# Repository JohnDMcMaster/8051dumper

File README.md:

# 8051dumper: Dump ROM contents from unprotected 8051 series processors.

This board and firmware allow the mask-programmed ROM contents to be dumped from
[Intel 8051 processors](https://en.wikipedia.org/wiki/Intel_MCS-51) and
derivatives/clones which do not include ROM readout protection mechanisms.

## Description

I wanted to dump out the firmware from the internal mask ROM of a Signetics
SCN8051H microcontroller in an ailing Micropolis 1325 (AKA DEC RD53-A) hard disk
drive. None of my programmers are able to do that, but there's a tricky way to
get early 8051 microcontrollers to dump out their own firmware. I made this
board to do it... and over-engineered the heck out of it, because why not! This
technique has been around for a long time. I didn't invent it. I just made this
board because I'd rather lay out a board than wire up stuff on a breadboard.

The 8051 has a pin called EA\# which tells it whether to fetch code from its
internal ROM (which is programmed at the metal mask layer at chip fabrication
time) or an external ROM. The trick is to put the 8051 into a circuit which
initially pulls EA\# low, so that the 8051 will boot from an external ROM with
our dumper code in it. That code immediately jumps out of the 4k address range
that is mapped to internal ROM when EA\# is high, and then uses a GPIO pin to
pull its own EA\# pin high and re-enable the internal mask ROM. At that point,
the 8051 conveniently fetches program memory accesses in the 0x0000-0x0FFF range
from the internal ROM, and fetches program memory accesses outside that range
from our external ROM. The special dumper code on our external ROM can then use
the MOVC function to read internal ROM bytes, and then dump them out somehow
(such as with the built-in serial port).

The 8052, 8054 and 8058 chips have larger internal ROM spaces, but otherwise
work the same way. Just for the heck of it, I put a knob on this board to tell
its firmware how much of the internal ROM space it should try to dump.

Later 8051 derivatives added features to prevent dumping their internal ROMs
easily, sunce as simply latching EA\# at reset time so that changing it later
doesn't do anything. This board can't work with any of those. It's only intended
to work with original Intel 8051 microcontrollers and exactl clones whose EA\#
pins behave the same way.

## Building the Board

You're on your own for assembling the board. You will need to program the
board's firmware into an AT28C256 (or plug-in equivalent) 32k x 8 (E(E))PROM.
Use the `firmware/8051dumper_filled.hex` image. This image contains the
necessary firmware for the 8051dumper board, with its unused areas filled with a
recognizable pattern to help you identify whether any given device under test is
dumping internal or external ROM contents.

## Using the Board

This board requires an external source of clean, regulated 5 VDC power, and some
sort of asynchronous serial interface with 5V TTL/CMOS signal levels. An FTDI
TTL-232R-5V cable can be pluged right into the header, or you can use clip
leads. The silkscreen markings identify the ground pin and the two data pins.

**There is no reverse-polarity protection, power regulation, or overvoltage protection on this board.** You need to connect the power correctly, or you will fry stuff. You can supply power through either the barrel jack or with clip leads
connected to the two test points.

Set your serial interface for 9600 baud, 8 data bits, no parity, and no flow
control. Use a terminal emulator or any other suitable software which can
capture the 9600 baud stream from 8051dumper.

Always make sure that the power switch is **OFF** before installing or removing
a device under test from 8051dumper.

If all goes well, when you turn on the board with a working [8051 (or other
MCS-51 series)](https://en.wikipedia.org/wiki/Intel_MCS-51) microcontroller
installed, the green START button will begin blinking and the serial port will
spit out `8051dumper v1.0 by NF6X`. If that doesn't happen at power-on, try
pressing the red RESET button to reset the microcontroller manually. If it still
doesn't happen, start debugging. Maybe the socket isn't making good contact?
Maybe, well, literally anything else has gone wrong?

Once the green START button is blinking, set the knob to the appropriate ROM
size and then press the green START button to begin the dump. While the dump is
in progress, the red RESET button will flash rapidly. When the dump is done, the
red RESET button will go dark and the green START button will light up. Now you
can turn off the board, or press RESET to do it all over again.

The 8051dumper output is in [Intel hex](https://en.wikipedia.org/wiki/Intel_HEX)
format. If you try dumping beyond the end of the internal ROM, or if you try
dumping from a device which latches EA\# at reset time, then some or all of the
output will be from the 8051dumper's own external ROM instead of the device
under test's internal ROM. To help you indentify when this happens, the unused
spaces of 8051dumper's ROM are filled with a pattern which is recognizable in
either hexadecimal or ASCII representations, and repeats every 16 bytes:

* Address (2 bytes)
* 0x00
* 0x80
* 0x51
* 0x00
* "8051dumper"

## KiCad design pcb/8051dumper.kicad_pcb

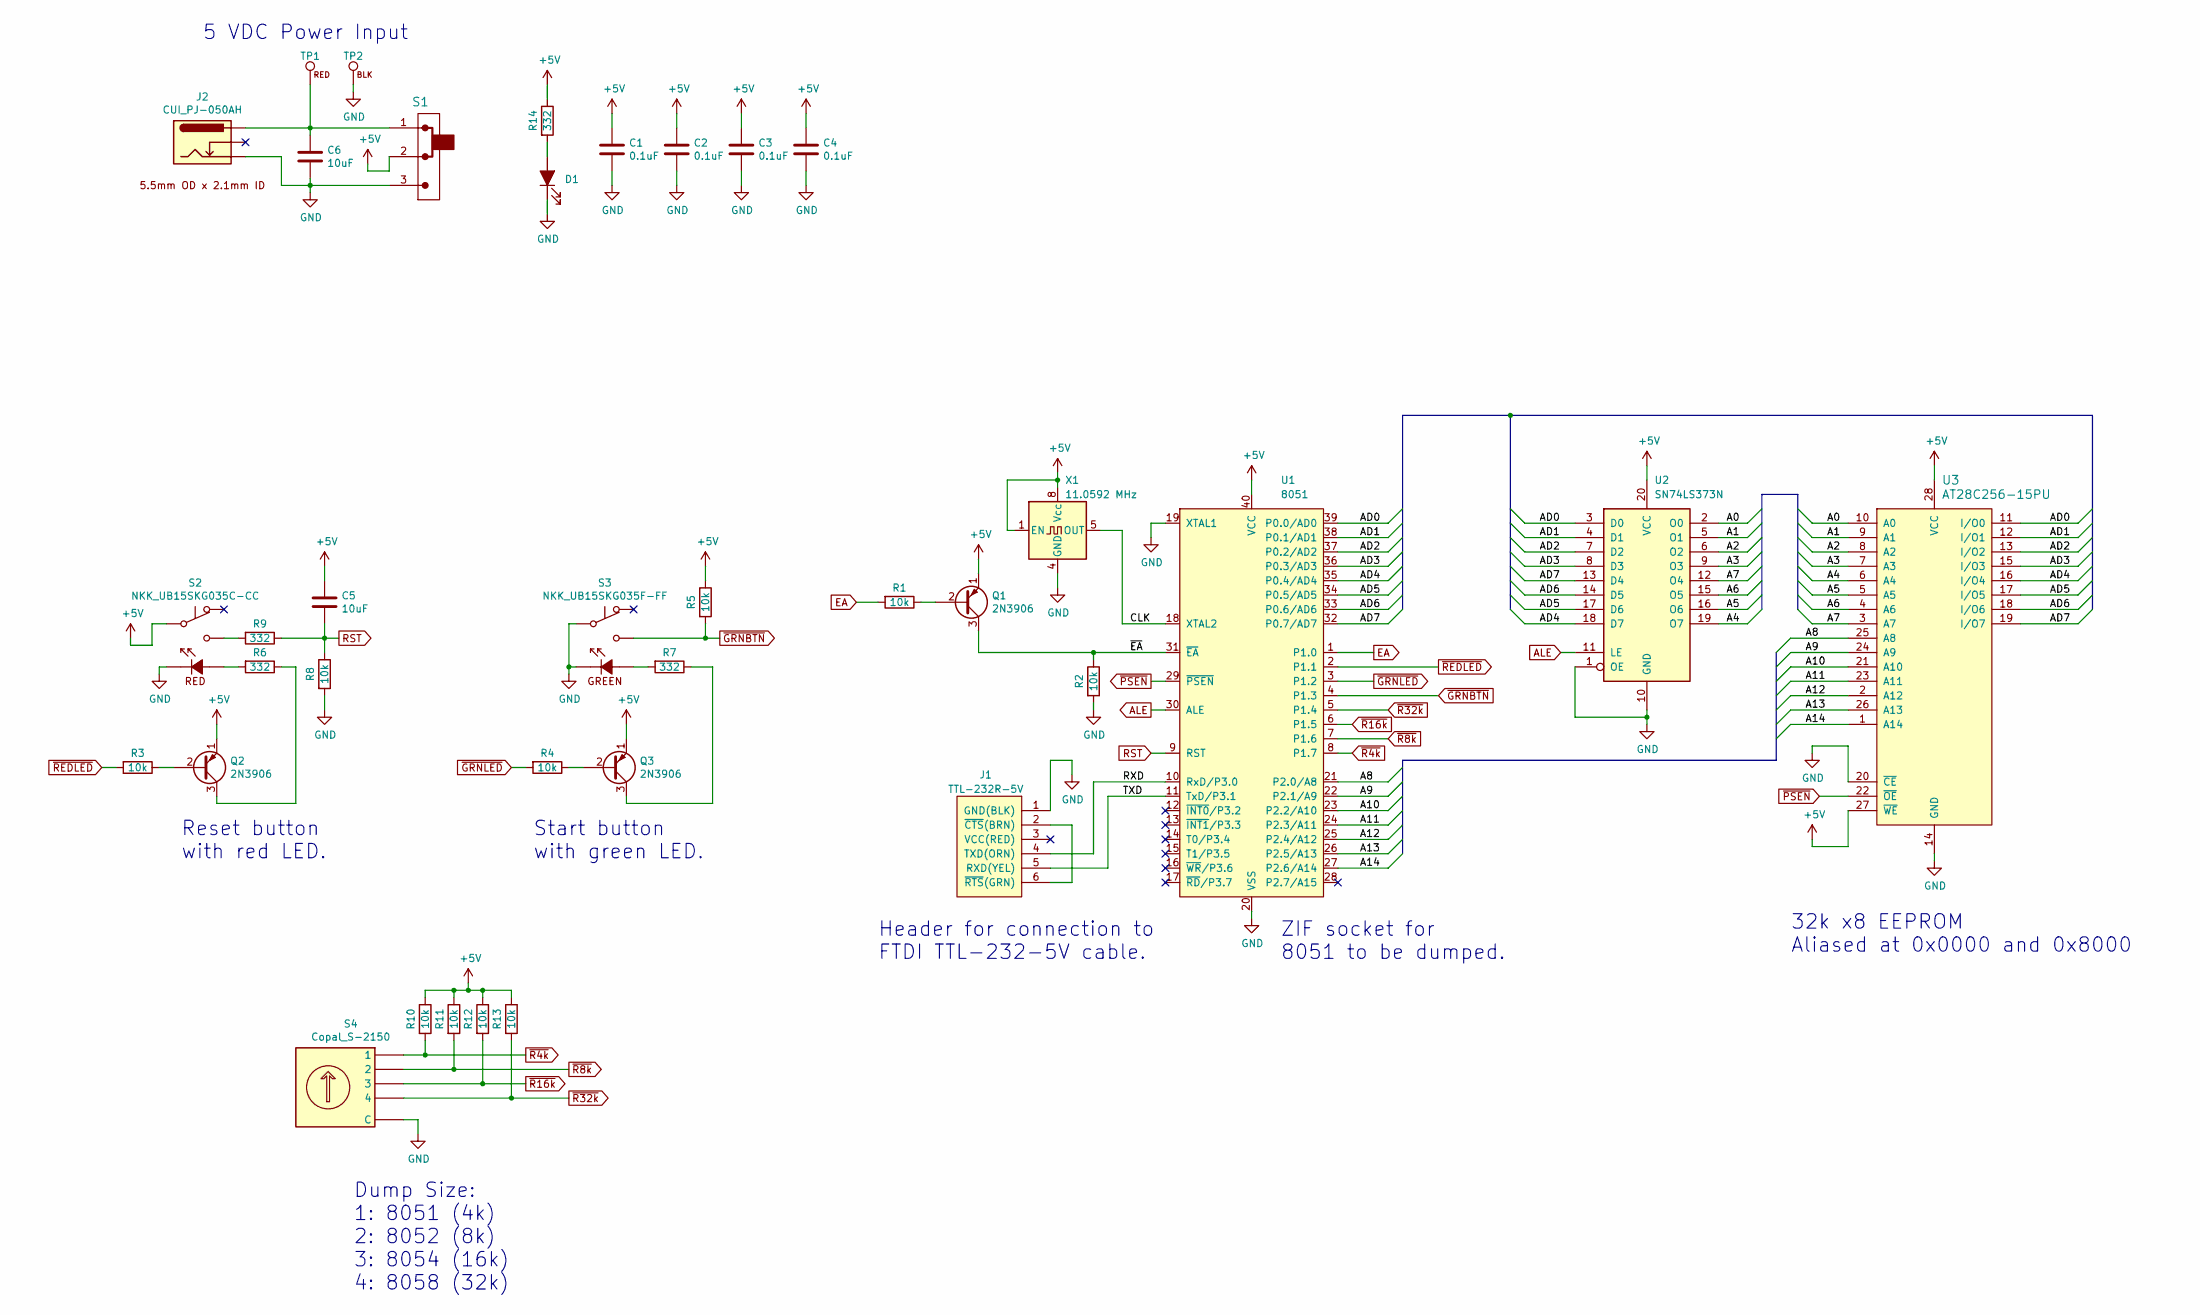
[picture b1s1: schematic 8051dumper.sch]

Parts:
C1, C2, C3, C4: 0.1uF; C_Disc_D3.8mm_W2.6mm_P2.50mm; MPN Vishay:K104K10X7RF5UL2
C5, C6: 10uF; C_Disc_D5.1mm_W3.2mm_P5.00mm; MPN TDK:FG24X7R1A106KRT06
D1: WP7113GD; LED_D5.0mm_Green_Kingbright_WP7113; MPN Kingbright:WP7113GD
J1: TTL-232R-5V; PinHeader_1x6_P2.54mm_Vertical_Unshrouded; MPN Sullins:PBC06SAAN
J2: CUI_PJ-050AH; BarrelJack_Horizontal_CUI_PJ-050AH; MPN CUI:PJ-050AH
Q1, Q2, Q3: 2N3906; TO-92_Inline_Wide; MPN ON Semiconductor:2N3906TF
R1, R2, R3, R4, R5, R8, R10, R11, R12, R13: 10k; R_Axial_DIN0207_L6.3mm_D2.5mm_P10.16mm_Horizontal; MPN Stackpole:RNF14FTD10K0
R6, R7, R9, R14: 332; R_Axial_DIN0207_L6.3mm_D2.5mm_P10.16mm_Horizontal; MPN Stackpole:RNF14FTD332R
S1: CK_1101M2S3CQE2; SW_CK_1101M2S3CQE2; MPN CK:1101M2S3CQE2
S2: NKK_UB15SKG035C-CC; SW_NKK_UB15SKG035C-CC; MPN NKK:UB15SKG035C-CC
S3: NKK_UB15SKG035F-FF; SW_NKK_UB15SKG035F-FF; MPN NKK:UB15SKG035F-FF
S4: Copal_S-2150; MPN Copal:S-2150
TP1: TestPoint_Mini_Red; TestPoint_Keystone_5000; MPN Keystone:5000
TP2: TestPoint_Mini_Black; TestPoint_Keystone_5001; MPN Keystone:5001
U1: 8051; DIP-40_W15.24mm_ZIF_Socket_Aries_40-6554-10; MPN Aries:40-6554-10
U2: SN74LS373N; DIP-20_W7.62mm; MPN TI:SN74LS373N
U3: AT28C256-15PU; DIP-28_W15.24mm_Socket; MPN Microchip:AT28C256-15PU
X1: 11.0592 MHz; Oscillator_DIP-8; MPN ECS:ECS-2200BX-110.5

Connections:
+5V: C1.1, C2.1, C3.1, C4.1, C5.1, Q1.1 (E), Q2.1 (E), Q3.1 (E), R5.1, R10.1, R11.1, R12.1, R13.1, R14.1, S1.2, S2.1 (COM), U1.40 (VCC), U2.20 (VCC), U3.27 (~WE), U3.28 (VCC), X1.1 (EN), X1.8 (Vcc)
/A0: U2.2 (O0), U3.10 (A0)
/A1: U2.5 (O1), U3.9 (A1)
/A2: U2.6 (O2), U3.8 (A2)
/A3: U2.9 (O3), U3.7 (A3)
/A4: U2.19 (O7), U3.6 (A4)
/A5: U2.16 (O6), U3.5 (A5)
/A6: U2.15 (O5), U3.4 (A6)
/A7: U2.12 (O4), U3.3 (A7)
/A8: U1.21 (P2.0/A8), U3.25 (A8)
/A9: U1.22 (P2.1/A9), U3.24 (A9)
/A10: U1.23 (P2.2/A10), U3.21 (A10)
/A11: U1.24 (P2.3/A11), U3.23 (A11)
/A12: U1.25 (P2.4/A12), U3.2 (A12)
/A13: U1.26 (P2.5/A13), U3.26 (A13)
/A14: U1.27 (P2.6/A14), U3.1 (A14)
/AD0: U1.39 (P0.0/AD0), U2.3 (D0), U3.11 (I/O0)
/AD1: U1.38 (P0.1/AD1), U2.4 (D1), U3.12 (I/O1)
/AD2: U1.37 (P0.2/AD2), U2.7 (D2), U3.13 (I/O2)
/AD3: U1.36 (P0.3/AD3), U2.8 (D3), U3.15 (I/O3)
/AD4: U1.35 (P0.4/AD4), U2.18 (D7), U3.16 (I/O4)
/AD5: U1.34 (P0.5/AD5), U2.17 (D6), U3.17 (I/O5)
/AD6: U1.33 (P0.6/AD6), U2.14 (D5), U3.18 (I/O6)
/AD7: U1.32 (P0.7/AD7), U2.13 (D4), U3.19 (I/O7)
/CLK: U1.18 (XTAL2), X1.5 (OUT)
/RXD: J1.4 (TXD(ORN)), U1.10 (RxD/P3.0)
/TXD: J1.5 (RXD(YEL)), U1.11 (TxD/P3.1)
/~EA: Q1.3 (C), R2.1, U1.31 (~EA)
ALE: U1.30 (ALE), U2.11 (LE)
EA: R1.2, U1.1 (P1.0)
GND: C1.2, C2.2, C3.2, C4.2, C6.2, D1.1 (K), J1.1 (GND(BLK)), J2.2, R2.2, R8.2, S1.3, S2.L- (K), S3.1 (COM), S3.L- (K), S4.C, TP2.1, U1.19 (XTAL1), U1.20 (VSS), U2.1 (OE), U2.10 (GND), U3.14 (GND), U3.20 (~CE), X1.4 (GND)
unnamed: C6.1, J2.1, S1.1, TP1.1
unnamed: D1.2 (A), R14.2
unnamed: J1.2 (~CTS~(BRN)), J1.6 (~RTS~(GRN))
unnamed: Q1.2 (B), R1.1
unnamed: Q2.2 (B), R3.1
unnamed: Q2.3 (C), R6.1
unnamed: Q3.2 (B), R4.1
unnamed: Q3.3 (C), R7.1
unnamed: R6.2, S2.L+ (A)
unnamed: R7.2, S3.L+ (A)
unnamed: R9.2, S2.2 (NO)
RST: C5.2, R8.1, R9.1, U1.9 (RST)
~GRNBTN: R5.2, S3.2 (NO), U1.4 (P1.3)
~GRNLED: R4.2, U1.3 (P1.2)
~PSEN: U1.29 (~PSEN), U3.22 (~OE)
~R4k: R10.2, S4.1, U1.8 (P1.7)
~R8k: R11.2, S4.2, U1.7 (P1.6)
~R16k: R12.2, S4.3, U1.6 (P1.5)
~R32k: R13.2, S4.4, U1.5 (P1.4)
~REDLED: R3.2, U1.2 (P1.1)

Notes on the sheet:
Header for connection to FTDI TTL-232-5V cable.
Reset button with red LED.
Start button with green LED.
ZIF socket for 8051 to be dumped.
5 VDC Power Input
Dump Size: 1: 8051 (4k) 2: 8052 (8k) 3: 8054 (16k) 4: 8058 (32k)
32k x8 EEPROM Aliased at 0x0000 and 0x8000

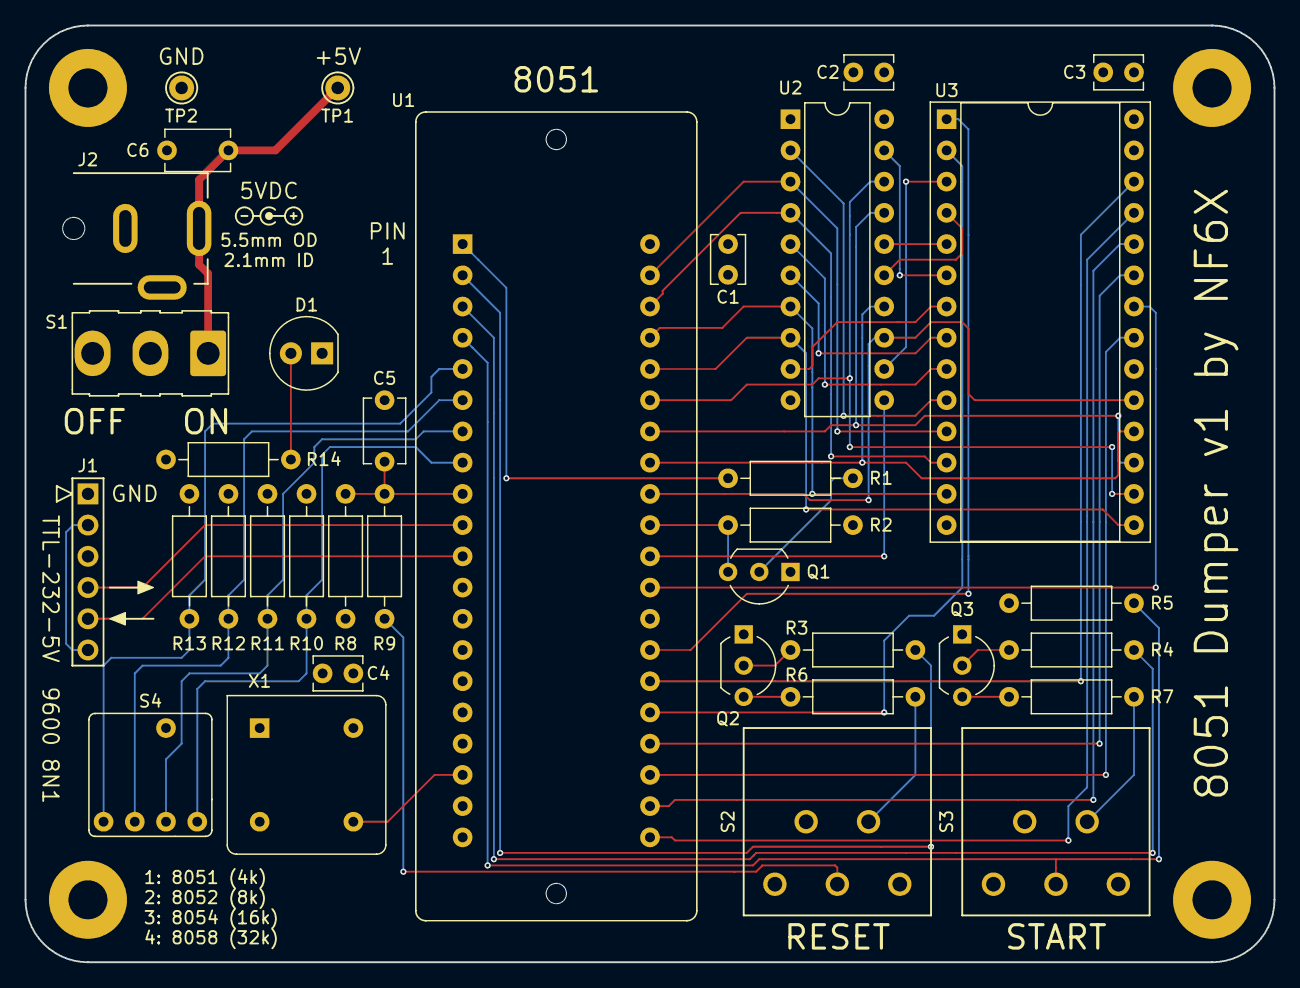
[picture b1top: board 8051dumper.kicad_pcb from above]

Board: 4 copper layers, 101.6 x 76.2 mm, 36 parts (0 on the bottom side), 51 nets.

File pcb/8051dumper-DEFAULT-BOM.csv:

MANUFACTURER,PARTNUM,QTY,REFS,IPN,VALUE,DESCRIPTION,FOOTPRINT,ALTERNATES
Aries,40-6554-10,1,U1,TBD,8051,,Package_DIP:DIP-40_W15.24mm_ZIF_Socket_Aries_40-6554-10,
CK,1101M2S3CQE2,1,S1,TBD,CK_1101M2S3CQE2,"SPDT slide switch, ON-ON",Button_Switch_THT:SW_CK_1101M2S3CQE2,
CUI,PJ-050AH,1,J2,TBD,CUI_PJ-050AH,"DC Barrel Jack,  5.5mm OD x 2.1mm ID, through hole, w/ switch",Connector_BarrelJack:BarrelJack_Horizontal_CUI_PJ-050AH,
Copal,S-2150,1,S4,TBD,Copal_S-2150,"Rotary switch, 4-position DIP 1P4T",Button_Switch_THT:Copal_S-2150,
ECS,ECS-2200BX-110.5,1,X1,TBD,11.0592 MHz,"Crystal Clock Oscillator, DIP8-style metal package",Oscillator:Oscillator_DIP-8,
Keystone,5000,1,TP1,TBD,TestPoint_Mini_Red,"Test point, 19x19mm 0.75x0.75in",TestPoint:TestPoint_Keystone_5000,
Keystone,5001,1,TP2,TBD,TestPoint_Mini_Black,"Test point, 19x19mm 0.75x0.75in",TestPoint:TestPoint_Keystone_5001,
Kingbright,WP7113GD,1,D1,TBD,WP7113GD,Light emitting diode,LED_THT:LED_D5.0mm_Green_Kingbright_WP7113,
Microchip,AT28C256-15PU,1,U3,TBD,AT28C256-15PU,,Package_DIP:DIP-28_W15.24mm_Socket,
NKK,UB15SKG035C-CC,1,S2,TBD,NKK_UB15SKG035C-CC,"Momentary button, SPDT, red LED, square red lens",Button_Switch_THT:SW_NKK_UB15SKG035C-CC,
NKK,UB15SKG035F-FF,1,S3,TBD,NKK_UB15SKG035F-FF,"Momentary button, SPDT, green LED, square green lens",Button_Switch_THT:SW_NKK_UB15SKG035F-FF,
ON Semiconductor,2N3906TF,3,Q1 Q2 Q3,TBD,2N3906,"PNP transistor, TO-92, 2N3906",Package_TO_SOT_THT:TO-92_Inline_Wide,
Stackpole,RNF14FTD10K0,10,R1 R2 R3 R4 R5 R8 R10 R11 R12 R13,TBD,10k,Resistor,Resistor_THT:R_Axial_DIN0207_L6.3mm_D2.5mm_P10.16mm_Horizontal,
Stackpole,RNF14FTD332R,4,R6 R7 R9 R14,TBD,332,Resistor,Resistor_THT:R_Axial_DIN0207_L6.3mm_D2.5mm_P10.16mm_Horizontal,
Sullins,PBC06SAAN,1,J1,TBD,TTL-232R-5V,Header for FTDI TTL-232R or equivalent,Connector_PinHeader_2.54mm:PinHeader_1x6_P2.54mm_Vertical_Unshrouded,
TDK,FG24X7R1A106KRT06,2,C5 C6,TBD,10uF,Unpolarized capacitor,Capacitor_THT:C_Disc_D5.1mm_W3.2mm_P5.00mm,
TI,SN74LS373N,1,U2,TBD,SN74LS373N,"8-bit Latch, 3-state outputs",Package_DIP:DIP-20_W7.62mm,
Vishay,K104K10X7RF5UL2,4,C1 C2 C3 C4,TBD,0.1uF,Unpolarized capacitor,Capacitor_THT:C_Disc_D3.8mm_W2.6mm_P2.50mm,

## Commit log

2020-05-06 Initial commit: v1 PCB and first blinky code.
2020-05-08 Add datasheets relevant to the project.
2020-05-08 Add pictures of first assembled board.
2020-05-10 First dumper code that seems to work with 8031 testing.
2020-05-10 Comment changes.
2020-05-10 Add user documentation.
2021-12-07 main.py: turnkey dumping
2021-12-07 gitignore: ignore hex and bin files
